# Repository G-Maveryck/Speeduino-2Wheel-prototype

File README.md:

# What is this ?
This project aim to build an Open-Source Engine Control Unit (aka ECU), fully programmable, accessible and modifiable, specificaly designed for motorcycles. It is still in "protoype" stage.
The goal is to end with a solution suited for retro-fit purposes : Lowering fuel consumption, pollution, and increased performances.

It's build around the DIY-EFI's CORE4 board, with a custom "Daughter board", and use the Speeduino firmware.
The CORE4 board is current choice for it's compact footprint, and fully featured board.
The Speeduino firmware can be found on it's own repo (See Licenses part for more informations.

# Electronics and Hardware parts
As the CORE4 is kind of a "all-in-one" solution, this current project focuses on building a "Daughter board" to "host" the CORE4.
The CORE4 board implement the Arduino and the speeduino board, in the same board and a compact form factor.

The goal of the Daughter-Board is to implement all the electronics needed to work correctly, and to be mounted easily on a bike.
It include a proper automotive connector, routing the sensors signals to the pin of the CORE4, and implement the essential electronics directly on the board (see the "Specific parts" section for more informations).

In this early state (v0.1), the ignitions drivers, VR Conditionner and MAP Sensor are mounted directly on the board.

An aditional project can be found in the repository, aiming to build an external ignition driver. This is currently not finished, but is on the roadmap. 
Two different ignition drivers are planned : Classic IGBT transistor driver for coils, and a CDI Module (Capacitive Discharge Ignition).

# Workflow & Tools
The electronics parts (PCB and Schematics) are designed using KiCad EDA 8.0.
A specific Kicad symbols and footprint library is made for this project, and can be found on this repo (see : "KiCad_Library" directory)
If the library does not relink automatically, you can add it manually with "KiCad > Preferences > Configure symbols/Footprint library > Add existing library" )

The other CAD parts (eg. enclosure, boxes, etc..) are designed using Solidworks 2023, and additionnaly distributed in .STEP and .STL file format.

# Specific parts
For the purposes of this project, some parts have been selected as "default" part. This includes :
- Main I/O connector : Molex CMC 48way  - Black (500762-0481 PCB Header / 64320-3311 Female connector)
- MAP Sensor : MPXHZ6250-AC6T1 from Freescale
- Ignition Coil Driver : build around FGP3440G2-F085 IGBT transistor from On-Semi.
- VR Conditionners : Based on the "Dual VR Conditionner" from the official Speeduino project, with the MAX9926 chip. In this case, the circuit is directly welded on the board.

# Licenses
This project is distributed under the terms of the "CERN Open Hardware Licence Version 2 - Strongly Reciprocal" License.
See LICENSE.md for more information.

It is based on many open-source contributions, mainly the Speeduino Project (github :  https://github.com/noisymime/speeduino / https://github.com/speeduino/Hardware) wich is distributed under CERN Open Hardware License v2 Strong (CERN-OHL-S) for hardware, and GPL-2.0 for the firmware.
All informations about the DIY-EFI's CORE4 can be found here : https://diy-efi.co.uk/knowledge-base/core4-universal-getting-started

# Support and Contribution
If you want to get involved in this project, feel free to contribute, clone or fork this repo. Feel free to submit a pull request if you have any contribution.
To join the developpement, please contact me at : wulveryck.gabriel@gmail.com (more information on my Github profile)
A lot of work still need to be done. This include building, testing, and building the best and also cheaper solution for specific uses !
All help is welcome !

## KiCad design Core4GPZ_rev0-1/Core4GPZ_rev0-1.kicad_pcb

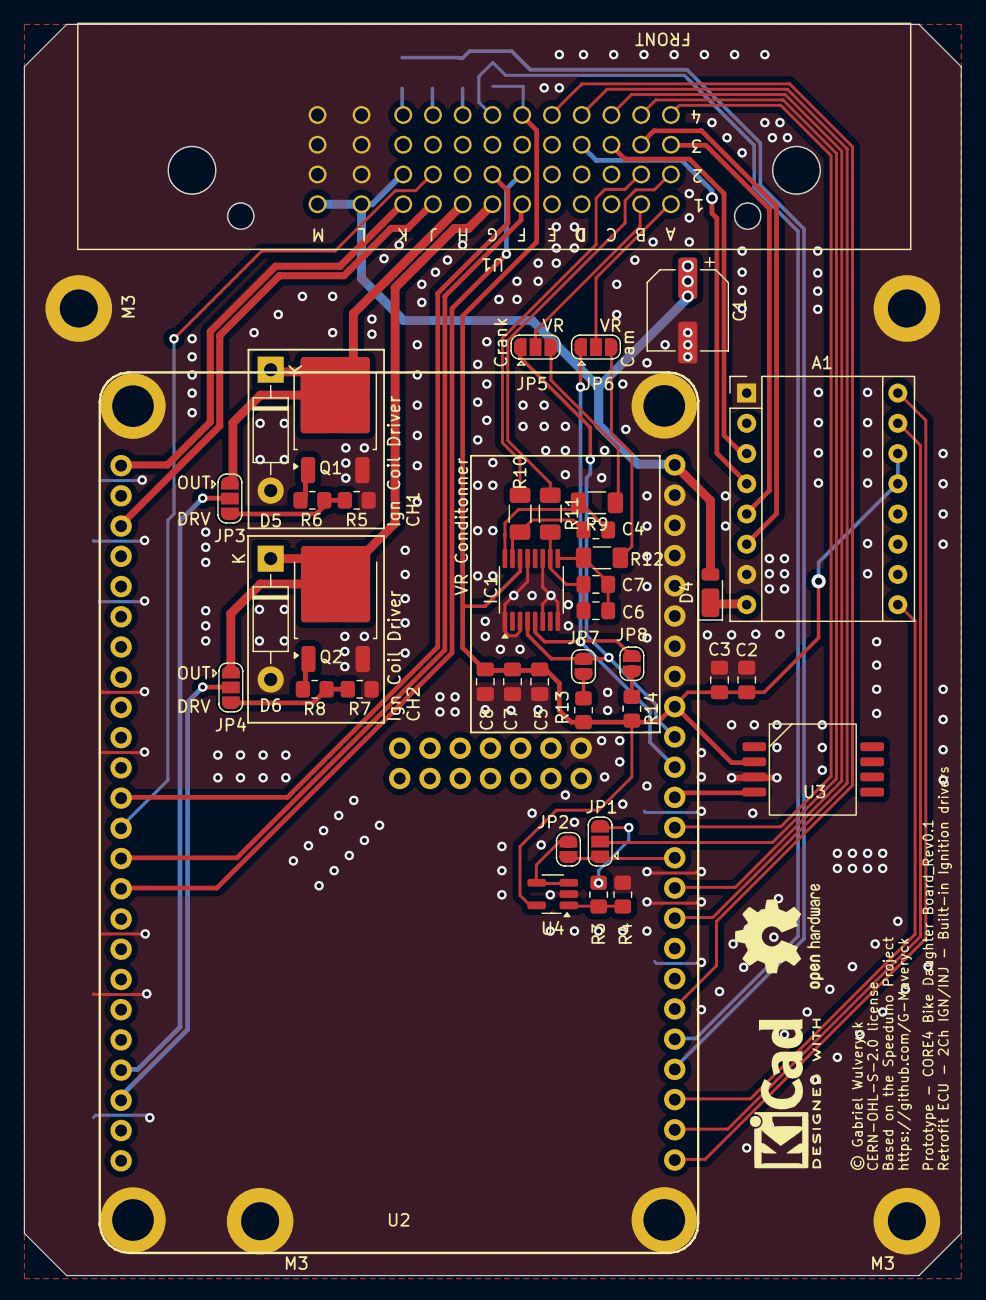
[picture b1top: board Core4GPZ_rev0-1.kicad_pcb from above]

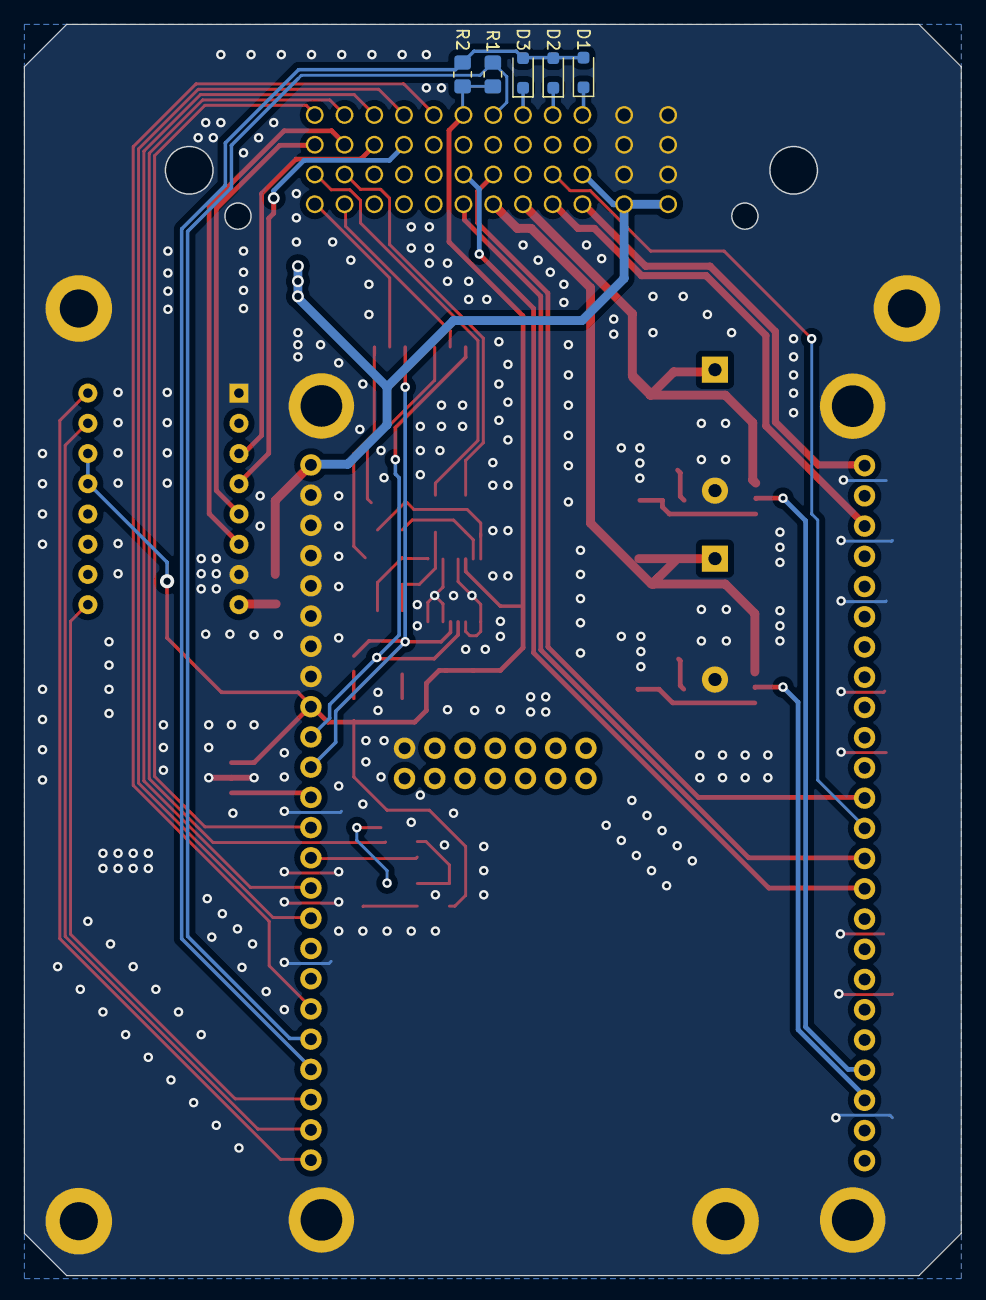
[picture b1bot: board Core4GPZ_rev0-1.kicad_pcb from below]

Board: 2 copper layers, 78.7 x 105.1 mm, 49 parts (5 on the bottom side), 54 nets.

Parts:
A1: Pololu_Breakout_DRV8825; Pololu_Breakout-16_15.2x20.3mm
C1: 100uF; CP_Elec_6.3x7.7
C2, C7: 100nF; C_0805_2012Metric_Pad1.18x1.45mm_HandSolder
C3, C8: 1uF; C_0805_2012Metric_Pad1.18x1.45mm_HandSolder
C4, C6, C7#2: 1nF; C_0805_2012Metric_Pad1.18x1.45mm_HandSolder
C5: 10nF; C_0805_2012Metric_Pad1.18x1.45mm_HandSolder
D1, D2, D3: 1N4448WX-TP; D_SOD-323_HandSoldering
D4: D_Schottky; D_PowerDI-123
D5, D6: 1N4007; D_DO-41_SOD81_P10.16mm_Horizontal
IC1: MAX9926UAEE_V+; QSOP-16_3.9x4.9mm_P0.635mm
JP1, JP3, JP4: SolderJumper_3_Open; SolderJumper-3_P1.3mm_Open_RoundedPad1.0x1.5mm
JP2: SolderJumper_2_Open; SolderJumper-2_P1.3mm_Open_RoundedPad1.0x1.5mm
JP5: CRANK - VR/Hall Selector; SolderJumper-3_P1.3mm_Open_RoundedPad1.0x1.5mm
JP6: CAM - VR/Hall Selector; SolderJumper-3_P1.3mm_Open_RoundedPad1.0x1.5mm
JP7: Crank Pull-Up; SolderJumper-2_P1.3mm_Open_RoundedPad1.0x1.5mm
JP8: Cam Pull-up; SolderJumper-2_P1.3mm_Open_RoundedPad1.0x1.5mm
M3, M3#2, M3#3, M3#4: MountingHole_3.2mm_M3_DIN965_Pad
Q1, Q2: FGD3440G2-F085; TO-252-2
R1, R2: 100k; R_0805_2012Metric_Pad1.20x1.40mm_HandSolder
R3: 660k; R_0805_2012Metric_Pad1.20x1.40mm_HandSolder
R4: 300K; R_0805_2012Metric_Pad1.20x1.40mm_HandSolder
R5, R7: 10k; R_0805_2012Metric_Pad1.20x1.40mm_HandSolder
R6, R8, R13, R14: 1k; R_0805_2012Metric_Pad1.20x1.40mm_HandSolder
R9, R10, R11, R12: 10k; R_1206_3216Metric_Pad1.30x1.75mm_HandSolder
U1: Molex_CMC_48pin_Male_Black
U2: core4_rev1; Core4
U3: MPXHZ6250AC6T1
U4: LMV321; SOT-23-5_HandSoldering

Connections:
/02_SNSR: U1.34 (4D), U2.40 (02)
/FAN_CTL: U1.16 (2F), U2.15 (FAN)
/FLEX_SNSR: U1.35 (4E), U2.43 (FLEX)
/FUEL_PUMP: U1.6 (1F), U2.14 (FUELP)
/IAT_SNSR: U1.33 (4C), U2.39 (IAT)
/IDLE_1: U1.17 (2G), U2.12 (IDLED1)
/INJ1_TRIG: U1.10 (1K), U2.1 (INJ1)
/INJ2_TRIG: U1.9 (1J), U2.3 (INJ2)
/TACHO_OUT: U1.19 (2J), U2.13 (TACHO)
/TPS_SNSR: U1.31 (4A), U2.37 (TPS)
BIKE_+12V_SWITCHED_IN: C1.1, D4.2 (A), U1.20 (2K), U1.41 (1L), U1.42 (1M), U2.25 (+12V)
CAM_SIGNAL: IC1.5 (COUT2), JP6.1 (A), JP8.1 (A), U2.35 (RPM2)
CAM_SNSR: JP6.2 (C), U1.1 (1A)
CAM_SNSR_VR-: R11.1, U1.11 (2A)
CLT_5V: JP1.1 (A), JP2.1 (A), U2.38 (CLT)
CLT_SNSR: JP1.2 (C), U1.32 (4B)
CRANK_SIGNAL: IC1.4 (COUT1), JP5.1 (A), JP7.1 (A), U2.34 (RPM1)
CRANK_SNSR: JP5.2 (C), U1.2 (1B)
CRANK_SNSR_VR-: R10.1, U1.12 (2B)
Clutch_SW: D2.1 (K), U1.39 (4J)
DIR: A1.16 (DIR), U2.48 (DIR)
EN: A1.9 (~EN), U2.46 (ENBL)
GND: A1.1 (GND), A1.7 (GND), C1.2, C2.2, C3.2, C5.2, C7.2, C8.2, D5.2 (A), D6.2 (A), IC1.1 (IN_THRS1), IC1.3 (BIAS1), IC1.6 (BIAS2), IC1.8 (INT_THRS2), IC1.11 (GND), IC1.13 (ZERO_EN), M3.1, M3#2.1, M3#3.1, M3#4.1, Q1.3 (E), Q2.3 (E), R4.2, R5.1, R7.1, U1.43 (2L), U1.44 (2M), U1.45 (3L), U1.46 (3M), U1.47 (4L), U1.48 (4M), U2.26 (EARTH), U2.27 (EARTH), U2.28 (EARTH), U2.29 (EARTH), U2.30 (EARTH), U2.31 (EARTH), U2.32 (EARTH), U2.61 (EARTH), U2.101, U2.102, U2.103, U2.104, U3.3 (GND), U4.2 (V-)
IGN_COIL1_DRIVE: D5.1 (K), JP3.1 (A), Q1.2 (C), U1.8 (1H)
IGN_COIL2_DRIVE: D6.1 (K), JP4.1 (A), Q2.2 (C), U1.7 (1G)
IGN_TRIG_1: JP3.2 (C), U2.21 (IGN1)
IGN_TRIG_2: JP4.2 (C), U2.22 (IGN2)
NEUTRAL_SW: D3.1 (K), U1.38 (4H)
unnamed: A1.8 (VMOT), D4.1 (K)
unnamed: C4.1, IC1.16 (IN1+), R9.2
unnamed: C4.2, IC1.15 (IN1-), R10.2
unnamed: C6.2, C7#2.2, IC1.9 (IN2+), R12.2
unnamed: C6.1, C7#2.1, IC1.10 (IN2-), R11.2
unnamed: JP1.3 (B), R3.1
unnamed: JP2.2 (B), U4.3 (-), U4.4
unnamed: JP3.3 (B), R5.2, R6.2
unnamed: JP4.3 (B), R7.2, R8.2
unnamed: JP5.3 (B), R9.1
unnamed: JP6.3 (B), R12.1
unnamed: JP7.2 (B), R13.1
unnamed: JP8.2 (B), R14.1
unnamed: Q1.1 (G), R6.1
unnamed: Q2.1 (G), R8.1
unnamed: U2.36 (MAP_IN), U3.4 (Vout)
unnamed: R3.2, R4.1, U4.1 (+)
SAFE_SIGNAL: D1.2 (A), D2.2 (A), D3.2 (A), R2.2, U2.45 (SPR_IN2)
SHIFT+: R1.2, U1.37 (4G), U2.44 (SPR_IN1)
SNSR_+5V: A1.13 (~RST), A1.14 (~SLP), C2.1, C3.1, C5.1, C7.1, C8.1, IC1.14 (VCC), R1.1, R2.1, R13.2, R14.2, U1.36 (4F), U2.33 (+5V), U3.2 (Vs), U4.5 (V+)
STEP: A1.15 (STEP), U2.47 (STEP)
SideStand_SW: D1.1 (K), U1.40 (4K)
Stepper_A1: A1.4 (A1), U1.24 (3D)
Stepper_A2: A1.3 (A2), U1.23 (3C)
Stepper_B1: A1.5 (B1), U1.21 (3A)
Stepper_B2: A1.6 (B2), U1.22 (3B)

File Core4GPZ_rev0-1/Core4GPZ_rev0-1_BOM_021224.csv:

"Reference","Value","Datasheet","Footprint","Qty","DNP"
"A1","Pololu_Breakout_DRV8825","https://www.pololu.com/product/2982","Module:Pololu_Breakout-16_15.2x20.3mm","1",""
"C1","100uF","~","Capacitor_SMD:CP_Elec_6.3x7.7","1",""
"C2,C7","100nF","~","Capacitor_SMD:C_0805_2012Metric_Pad1.18x1.45mm_HandSolder","2",""
"C3,C8","1uF","~","Capacitor_SMD:C_0805_2012Metric_Pad1.18x1.45mm_HandSolder","2",""
"C4,C6","1nF","~","Capacitor_SMD:C_0805_2012Metric_Pad1.18x1.45mm_HandSolder","2",""
"C5","10nF","~","Capacitor_SMD:C_0805_2012Metric_Pad1.18x1.45mm_HandSolder","1",""
"D1,D2,D3","1N4448WX-TP","~","Diode_SMD:D_SOD-323_HandSoldering","3",""
"D4","D_Schottky","~","Diode_SMD:D_PowerDI-123","1",""
"D5,D6","1N4007","~","Diode_THT:D_DO-41_SOD81_P10.16mm_Horizontal","2",""
"IC1","MAX9926UAEE_V+","https://componentsearchengine.com/Datasheets/1/MAX9926UAEE_V+.pdf","Package_SO:QSOP-16_3.9x4.9mm_P0.635mm","1",""
"Q1,Q2","FGD3440G2-F085","~","Package_TO_SOT_SMD:TO-252-2","2",""
"R1,R2","100k","~","Resistor_SMD:R_0805_2012Metric_Pad1.20x1.40mm_HandSolder","2",""
"R3","660k","~","Resistor_SMD:R_0805_2012Metric_Pad1.20x1.40mm_HandSolder","1",""
"R4","300K","~","Resistor_SMD:R_0805_2012Metric_Pad1.20x1.40mm_HandSolder","1",""
"R5,R7,R9,R10,R11,R12","10k","~","-- valeurs mixtées --","6",""
"R6,R8,R13,R14","1k","~","Resistor_SMD:R_0805_2012Metric_Pad1.20x1.40mm_HandSolder","4",""
"U1","~","https://www.molex.com/en-us/products/part-detail/5007620481","Bike_Prototype_LIB:Molex_CMC_48pin_Male_Black","1",""
"U2","core4_rev1","https://diy-efi.co.uk/knowledge-base/core4-universal-getting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","Bike_Prototype_LIB:Core4","1",""
"U3","MPXHZ6250AC6T1","https://www.nxp.com/docs/en/data-sheet/MPXH6250A.pdf","Bike_Prototype_LIB:MPXHZ6250AC6T1","1",""
"U4","LMV321","http://www.ti.com/lit/ds/symlink/lmv324.pdf","Package_TO_SOT_SMD:SOT-23-5_HandSoldering","1",""

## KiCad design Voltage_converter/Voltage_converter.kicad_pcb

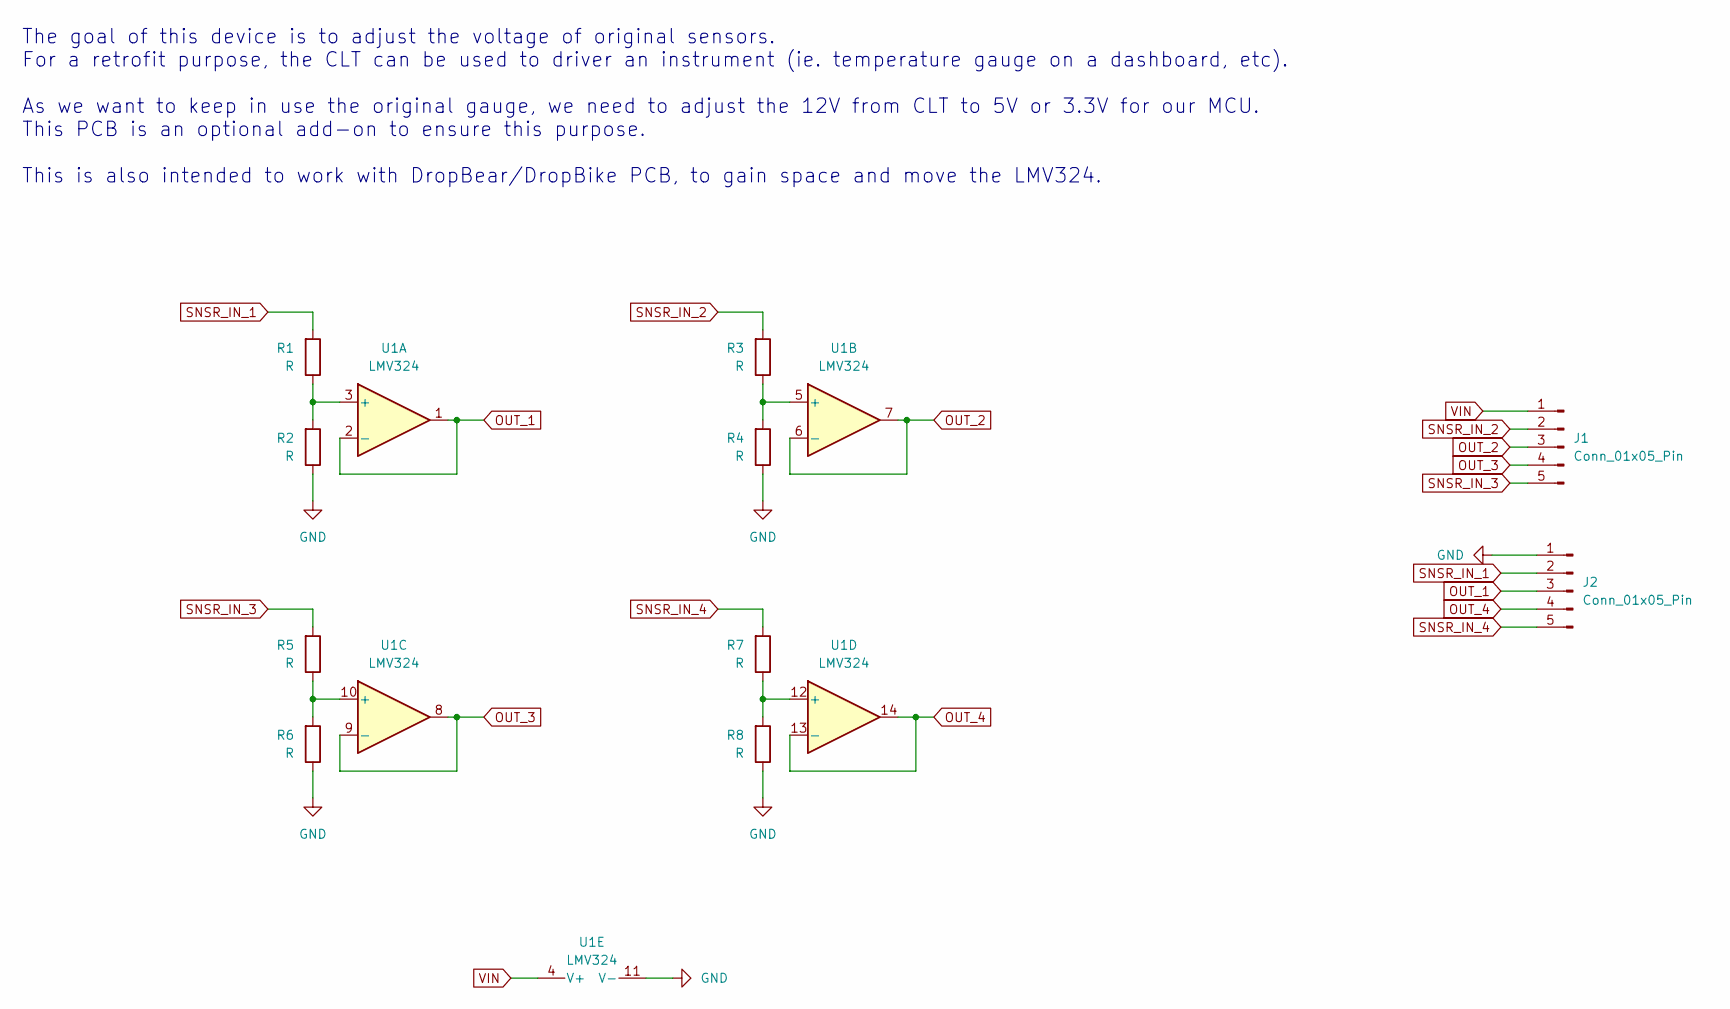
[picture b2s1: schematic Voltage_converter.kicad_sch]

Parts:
J1, J2: Conn_01x05_Pin; PinHeader_1x05_P2.54mm_Vertical
R1, R2, R3, R4, R5, R6, R7, R8: R; R_0805_2012Metric_Pad1.20x1.40mm_HandSolder
U1: LMV324; SOIC-14_3.9x8.7mm_P1.27mm

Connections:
GND: J2.1, R2.1, R4.1, R6.1, R8.1, U1.11 (V-)
unnamed: R1.1, R2.2, U1.3 (+)
unnamed: R3.1, R4.2, U1.5 (+)
unnamed: R5.1, R6.2, U1.10 (+)
unnamed: R7.1, R8.2, U1.12 (+)
OUT_1: J2.3, U1.1, U1.2 (-)
OUT_2: J1.3, U1.6 (-), U1.7
OUT_3: J1.4, U1.8, U1.9 (-)
OUT_4: J2.4, U1.13 (-), U1.14
SNSR_IN_1: J2.2, R1.2
SNSR_IN_2: J1.2, R3.2
SNSR_IN_3: J1.5, R5.2
SNSR_IN_4: J2.5, R7.2
VIN: J1.1, U1.4 (V+)

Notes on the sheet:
The goal of this device is to adjust the voltage of original sensors. For a retrofit purpose, the CLT can be used to driver an instrument (ie. temperature gauge on a dashboard, etc). As we want to keep in use the original gauge, we need to adjust the 12V from CLT to 5V or 3.3V for our MCU. This PCB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

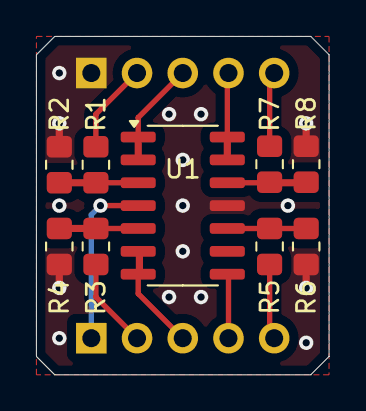
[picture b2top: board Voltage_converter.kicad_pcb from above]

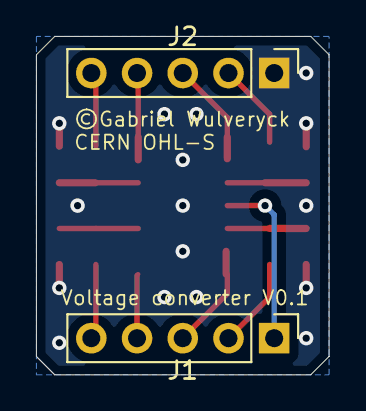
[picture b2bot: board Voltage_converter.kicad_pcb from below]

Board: 2 copper layers, 16.3 x 18.8 mm, 11 parts (2 on the bottom side), 14 nets.

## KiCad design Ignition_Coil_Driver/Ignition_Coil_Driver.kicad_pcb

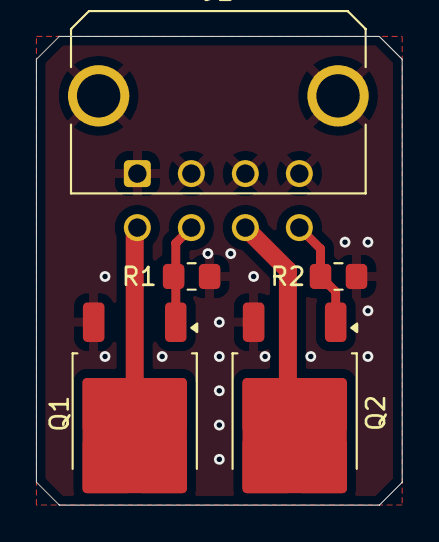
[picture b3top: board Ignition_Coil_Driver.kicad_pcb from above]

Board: 2 copper layers, 20.3 x 26.0 mm, 5 parts (0 on the bottom side), 5 nets.

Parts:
J1: Conn_02x04_Row_Letter_First; Molex_Micro-Fit_3.0_43045-0821_2x04-1MP_P3.00mm_Horizontal
Q1, Q2: FGD3440G2-F085; TO-252-2
R1, R2: 1k; R_0805_2012Metric_Pad1.20x1.40mm_HandSolder

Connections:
COIL1_Drive: J1.5, Q1.2 (C)
COIL2_Drive: J1.7, Q2.2 (C)
GND: J1.1, J1.2, J1.3, J1.4, J1.MP, Q1.3 (E), Q2.3 (E), R1.2, R2.2
IGN_TRIG_1: J1.6, Q1.1 (G), R1.1
IGN_TRIG_2: J1.8, Q2.1 (G), R2.1

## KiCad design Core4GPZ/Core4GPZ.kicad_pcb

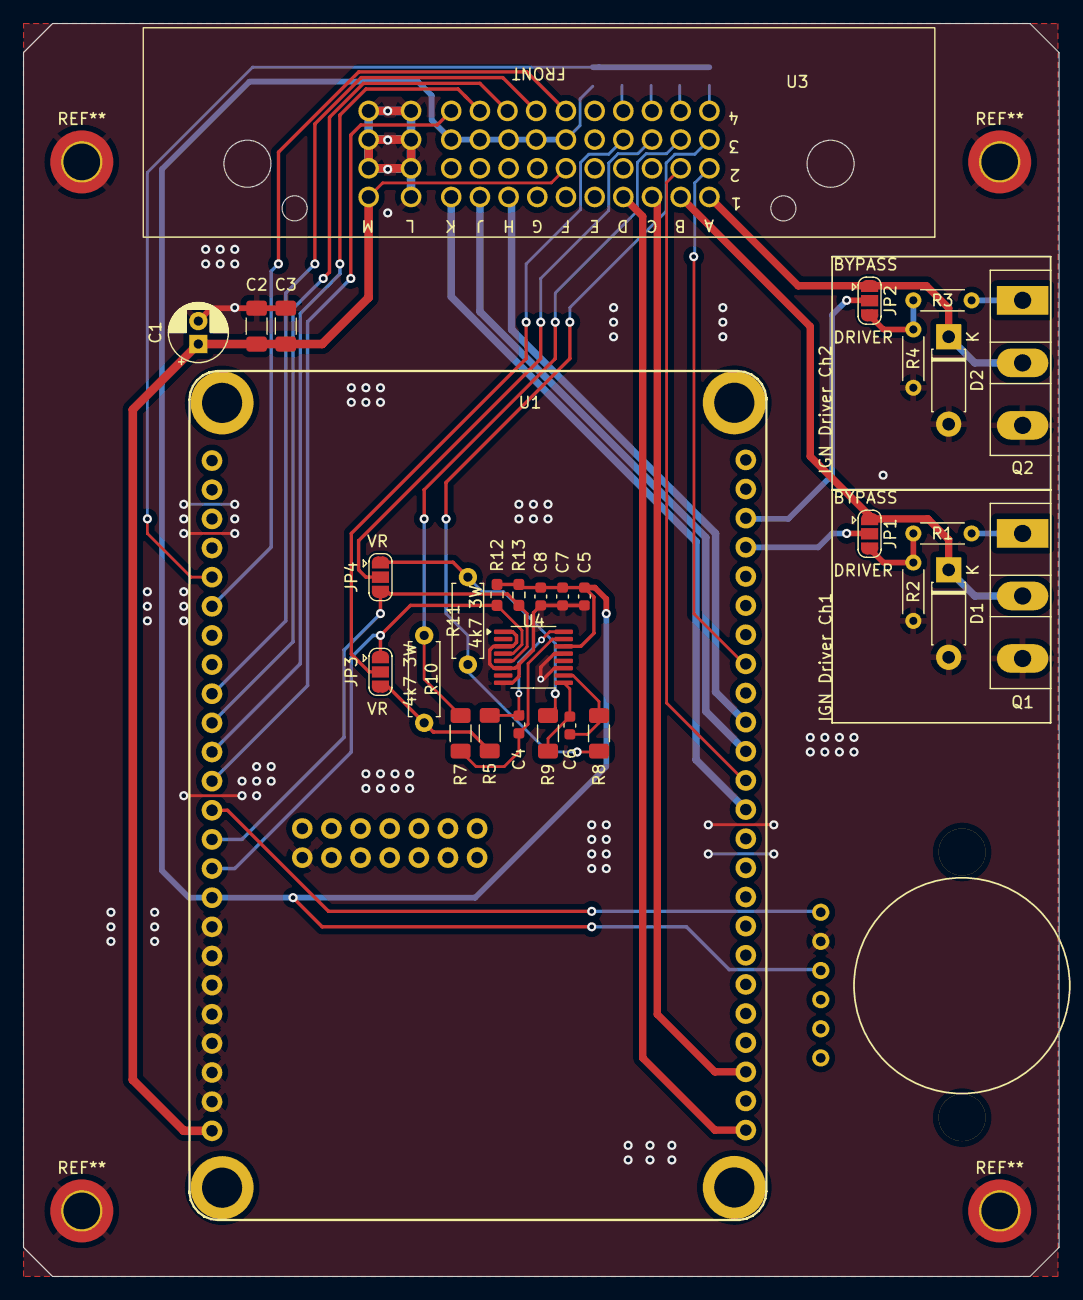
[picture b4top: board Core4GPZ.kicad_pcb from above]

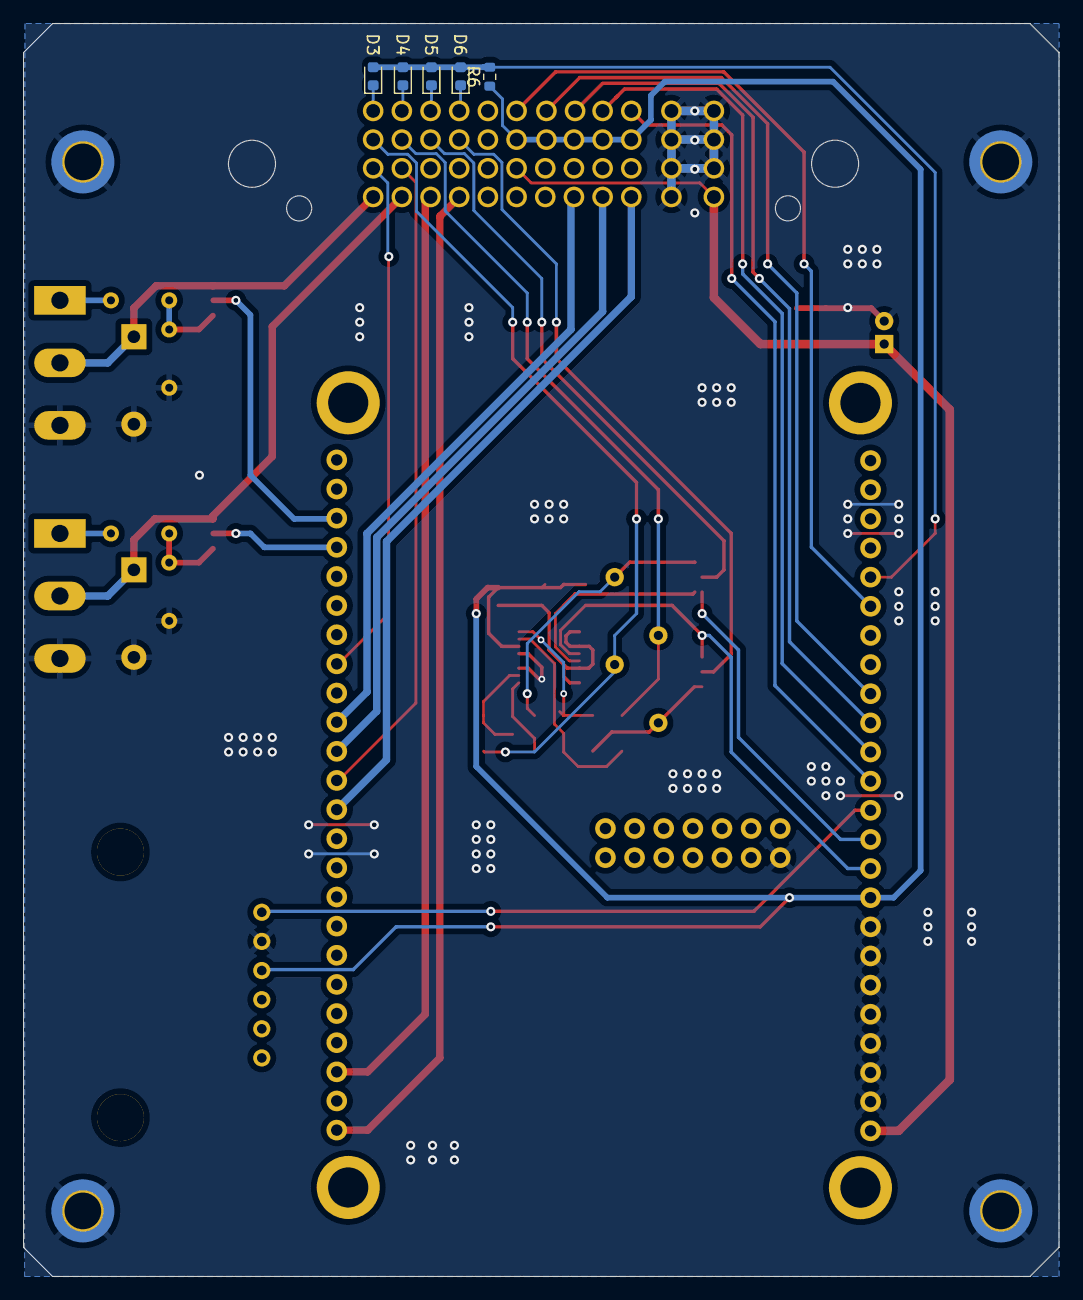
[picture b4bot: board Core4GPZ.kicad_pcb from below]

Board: 2 copper layers, 90.3 x 109.2 mm, 37 parts (5 on the bottom side), 41 nets.

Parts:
C1: 10uF; CP_Radial_D5.0mm_P2.00mm
C2: 100nF; C_1206_3216Metric_Pad1.33x1.80mm_HandSolder
C3: 1nF; C_1206_3216Metric_Pad1.33x1.80mm_HandSolder
C4, C6: 1n; C_0603_1608Metric
C5: 10n; C_0603_1608Metric
C7: 100n; C_0603_1608Metric
C8: 1u; C_0603_1608Metric
D1, D2: 1N4007; D_DO-41_SOD81_P7.62mm_Horizontal
D3, D4, D5, D6: D; D_0603_1608Metric
JP1, JP2: SolderJumper_3_Open; SolderJumper-3_P1.3mm_Open_RoundedPad1.0x1.5mm
JP3: Crank - VR/Hall Selector; SolderJumper-3_P1.3mm_Open_RoundedPad1.0x1.5mm
JP4: Cam - VR/Hall Selector; SolderJumper-3_P1.3mm_Open_RoundedPad1.0x1.5mm
Q1, Q2: IRG4PF50W; TO-247-3_Vertical
R1, R3: 1k; R_Axial_DIN0204_L3.6mm_D1.6mm_P5.08mm_Horizontal
R2, R4: 10k; R_Axial_DIN0204_L3.6mm_D1.6mm_P5.08mm_Horizontal
R5, R7, R8, R9: 10k; R_1206_3216Metric_Pad1.30x1.75mm_HandSolder
R6: 100k; R_0603_1608Metric
R10, R11: 4.7k; R_Axial_DIN0207_L6.3mm_D2.5mm_P7.62mm_Horizontal
R12, R13: 1k; R_0603_1608Metric_Pad0.98x0.95mm_HandSolder
U1: core4; Core4
U2: MPX4250
U3: Molex_CMC_48pin_Male_Black
U4: MAX9926UAEE+; QSOP-16_3.9x4.9mm_P0.635mm

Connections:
/02_SNSR: U1.40 (02), U3.37 (4G)
/CLT_SNSR: U1.38 (CLT), U3.39 (4J)
/FAN_CTL: U1.15 (FAN), U3.8 (1H)
/FLEX_SNSR: U1.43 (FLEX), U3.36 (4F)
/FUEL_PUMP: U1.14 (FUELP), U3.9 (1J)
/IAT_SNSR: U1.39 (IAT), U3.38 (4H)
/IDLE_1: U1.12 (IDLED1), U3.10 (1K)
/INJ1_TRIG: U1.1 (INJ1), U3.4 (1D)
/INJ2_TRIG: U1.3 (INJ2), U3.3 (1C)
/NEUTRAL_LIGHT: U1.17 (D36), U3.11 (2A)
/TACHO: U1.13 (TACHO), U3.12 (2B)
/TPS_SNSR: U1.37 (TPS), U3.40 (4K)
BIKE_+12V_SWITCHED_IN: C1.1, C2.1, C3.1, U1.25 (+12V), U3.16 (2F), U3.42 (1M)
BIKE_GROUND: C1.2, C2.2, C3.2, C5.2, C7.2, C8.2, D1.2 (A), D2.2 (A), Q1.3 (E), Q2.3 (E), R2.2, R4.2, U1.26 (EARTH), U1.27 (EARTH), U1.28 (EARTH), U1.29 (EARTH), U1.30 (EARTH), U1.31 (EARTH), U1.32 (EARTH), U1.61 (EARTH), U2.2 (GND), U3.41 (1L), U3.43 (2L), U3.44 (2M), U3.45 (3L), U3.46 (3M), U3.47 (4L), U3.48 (4M), U4.1 (INT_THRS1), U4.3 (BIAS1), U4.6 (BIAS2), U4.8 (INT_THRS2), U4.11 (GND), U4.13 (ZERO_EN)
CAM_SIGNAL: JP4.3 (B), R13.2, U1.35 (RPM2), U4.5 (COUT2)
CAM_SNSR: JP4.2 (C), U3.23 (3C)
CAM_SNSR_VR-: R8.2, R11.2, U3.21 (3A)
CLT_+5V: C5.1, C7.1, C8.1, R6.1, R12.1, R13.1, U1.33 (+5V), U2.3 (VCC), U3.26 (3F), U3.27 (3G), U3.28 (3H), U3.29 (3J), U3.30 (3K), U4.14 (VCC)
CRANK_SIGNAL: JP3.1 (A), R12.2, U1.34 (RPM1), U4.4 (COUT1)
CRANK_SNSR: JP3.2 (C), U3.24 (3D)
CRANK_SNSR_VR-: R7.2, R10.2, U3.22 (3B)
Clutch_SWITCH: D5.1 (K), U3.33 (4C)
IGN_COIL1_DRIVE: D1.1 (K), JP1.1 (A), Q1.2 (C), U3.2 (1B)
IGN_COIL2_DRIVE: D2.1 (K), JP2.1 (A), Q2.2 (C), U3.1 (1A)
IGN_TRIG_1: JP1.2 (C), U1.21 (IGN1)
IGN_TRIG_2: JP2.2 (C), U1.22 (IGN2)
unnamed: JP1.3 (B), R1.2, R2.1
unnamed: JP2.3 (B), R3.2, R4.1
unnamed: JP3.3 (B), R5.2, R10.1
unnamed: JP4.1 (A), R9.2, R11.1
unnamed: Q1.1 (G), R1.1
unnamed: Q2.1 (G), R3.1
unnamed: U1.36 (MAP_IN), U2.1 (VOUT)
unnamed: C4.1, R5.1, U4.16 (IN1+)
unnamed: C4.2, R7.1, U4.15 (IN1-)
unnamed: C6.2, R9.1, U4.9 (IN2+)
unnamed: C6.1, R8.1, U4.10 (IN2-)
Neutral_SWITCH: D4.1 (K), U3.32 (4B)
SAFE_SIGNAL: D3.2 (A), D4.2 (A), D5.2 (A), D6.2 (A), R6.2, U1.44 (SPR_IN1)
SPR1_SWITCH: D6.1 (K), U3.34 (4D)
SideStand_SWITCH: D3.1 (K), U3.31 (4A)

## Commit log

2024-02-24 Add a splited CDI module. First Design of Ignition coil driver
2024-03-17 Updated security wiring and changed IGN driver for MOSFET
2024-03-23 First Drawing of High volatage generator part
    First Drawing of High volatage generator part
2024-03-26 Changed Connectors for Molex CMC 48pins Black.
    Changed ECU Connector for Molex CMC 48pins Black, for compacity and cost reduction. Designed custom Footprint for this purpose
2024-03-27 Test montage générateur de Haute tension
2024-03-31 Redraw CDI pwr Supply with Boost circuit for 48v output
2024-04-04 Updated to Kicad 8.0
    Also added Highvoltage circuit
2024-04-05 Added documentation for Molex Connector
2024-04-27 Work in progress
2024-05-03 Added VR Conditionner for Cam/Crank SNSR
    Added some jumper for prototyping and testing purposes
2024-05-08 Started Implementation of VR Conditionner
2024-05-16 Implemented VR_Conditionner (MAX9926+)
    First look at ground plane
2024-06-18 Added rev0.1 dir
    Aim to re draw a cleaner PCB, with cleaner routes
2024-06-18 Frist revision
    First revision finished, optimised routing, board turned 180°.
2024-06-18 Tiny modification
    ???
2024-06-19 Finalized ground planes
    Added CORE4 pads to ground
2024-07-25 Rewied ground plane, set all SNSR+5V ref to one pin
2024-07-25 Designed a minimal external coil driver
2024-07-25 Added informations for Molex CMC conn
2024-07-27 Create LICENSE.md
    Moved to CERN-OHL-S
2024-07-27 Deleted first version (outdated)
2024-07-27 Added first enclosure design
2024-07-28 Added CAD enclosure .step and .stl
2024-08-13 Reworked the VR conditionner
    Schematic and PCB based on the Dropbear model
2024-08-14 Moved VR Conditionner.
2024-08-15 Moved +12V decoupling capacitors
2024-08-18 Changed MAP sensors for MPXHZ6250AC6T1
2024-08-29 Modified GND Plane. Reworked routing
2024-09-10 Started implementing Stepper driver
    DRV8825 breakout board
2024-09-12 Implemented DRV8825 and upgrade IGN Driver
    Ignition drivers upgraded with SMD IGBT FGD3440
    Added Stepper Driver DRV8825
2024-09-13 Reduced board width
    moved IGN Driver under the Core4 to reduce overall board size
2024-09-26 Minor visual modifications
2024-10-16 Added AOP for a proper decoupling for CLT
    Modified Fixing point and dimensions on the enclosure
2024-10-17 Removed NeutralSwitch. Added Up-Shifter support
2024-10-22 Reorganised Schematic
2024-10-23 Added pullup resistor on VR Conditionner
2024-11-12 Added Gerber files
2024-11-26 Updated CAD Enclosure STL and STEP export
2024-11-27 Updated component Library with specific parts
    Added "Speeduino_bike_prototype" library, with symbols and footprints.
    You can add this library to your library table.
2024-11-27 Updated gerber, updated BOM
    Also added preview files in JPG
2024-11-27 Updated components library
    Added documentation and datasheet in components properties
2024-11-29 Update README.md
    Added preview images and corect some spelling errors
2024-12-02 Updated project library, BOM and documentation

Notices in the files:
Core4GPZ_rev0-1/Core4GPZ_rev0-1.kicad_pcb:
© Gabriel Wulveryck
CERN-OHL-S-2.0 license
Voltage_converter/Voltage_converter.kicad_pcb:
CERN OHL-S
